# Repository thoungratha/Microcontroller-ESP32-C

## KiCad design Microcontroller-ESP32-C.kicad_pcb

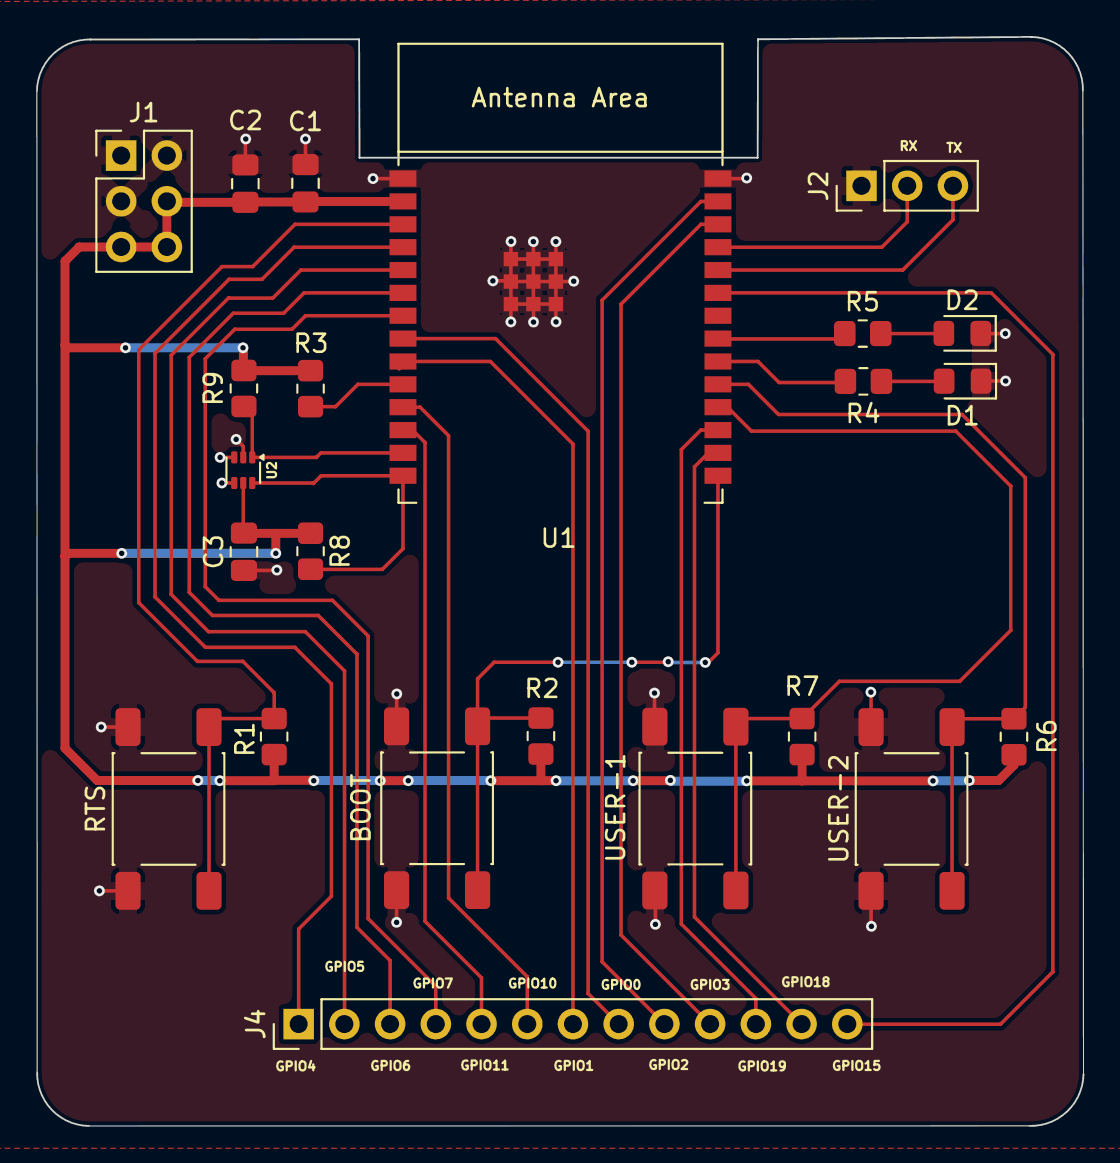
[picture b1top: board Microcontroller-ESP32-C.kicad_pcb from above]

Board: 2 copper layers, 58.1 x 60.5 mm, 23 parts (0 on the bottom side), 28 nets.

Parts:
BOOT: Button_Boot; SW_Push_1P1T_NO_E-Switch_TL3301NxxxxxG
C1: 10uF; C_0805_2012Metric_Pad1.18x1.45mm_HandSolder
C2, C3: 0.1uF; C_0805_2012Metric_Pad1.18x1.45mm_HandSolder
D1, D2: LED; LED_0805_2012Metric_Pad1.15x1.40mm_HandSolder
J1: Power_Connector; PinHeader_2x03_P2.54mm_Vertical
J2: Conn_01x03; PinHeader_1x03_P2.54mm_Vertical
J4: Conn_01x13; PinHeader_1x13_P2.54mm_Vertical
R1, R2, R3, R4, R5, R6, R7: 10k; R_0805_2012Metric_Pad1.20x1.40mm_HandSolder
R8, R9: 5k; R_0805_2012Metric_Pad1.20x1.40mm_HandSolder
RTS: Button_RST; SW_Push_1P1T_NO_E-Switch_TL3301NxxxxxG
U1: ESP32-C6-WROOM-1
U2: TMP112xxDRL; SOT-563
USER-1: USER_1; SW_Push_1P1T_NO_E-Switch_TL3301NxxxxxG
USER-2: USER_2; SW_Push_1P1T_NO_E-Switch_TL3301NxxxxxG

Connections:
3V3: C1.2, C2.2, C3.2, J1.4, J1.5, J1.6, R1.1, R2.2, R3.2, R6.2, R7.2, R8.1, R9.1, U1.2 (3V3), U2.5 (V+)
GND: BOOT.2, C1.1, C2.1, C3.1, D1.1 (K), D2.1 (K), J1.1, J1.2, J1.3, J2.1, RTS.1, U1.1 (GND), U1.28 (GND), U1.29 (GND), U2.2 (GND), U2.3 (ALERT), U2.4 (ADD0), USER-1.2, USER-2.2
GPIO0: J4.8, U1.8 (GPIO0/ADC1_CH0/XTAL_32K_P)
GPIO1: J4.7, U1.9 (GPIO1/ADC1_CH1/XTAL_32K_N)
GPIO2: J4.9, U1.27 (GPIO2/ADC1_CH2)
GPIO3: J4.10, U1.26 (GPIO3/ADC1_CH3)
GPIO4: J4.1, U1.4 (MTMS/GPIO4/ADC1_CH4)
GPIO5: J4.2, U1.5 (MTDI/GPIO5/ADC1_CH5)
GPIO6: J4.3, U1.6 (MTCK/GPIO6/ADC1_CH6)
GPIO7: J4.4, U1.7 (MTDO/GPIO7)
GPIO10: J4.6, U1.11 (GPIO10)
GPIO11: J4.5, U1.12 (GPIO11)
GPIO12: R9.2, U1.13 (GPIO12/USB_D-), U2.1 (SCL)
GPIO13: R8.2, U1.14 (GPIO13/USB_D+), U2.6 (SDA)
GPIO15: J4.13, U1.23 (GPIO15)
GPIO18: J4.12, U1.16 (GPIO18)
GPIO19: J4.11, U1.17 (GPIO19)
unnamed: D1.2 (A), R4.1
unnamed: D2.2 (A), R5.1
unnamed: R1.2, RTS.2, U1.3 (EN/CHIP_PU)
unnamed: R3.1, U1.10 (GPIO8)
unnamed: BOOT.1, R2.1, U1.15 (GPIO9)
unnamed: R7.1, U1.18 (GPIO20), USER-1.1
unnamed: R6.1, U1.19 (GPIO21), USER-2.1
unnamed: R4.2, U1.20 (GPIO22)
unnamed: R5.2, U1.21 (GPIO23)
UART0-RX: J2.3, U1.24 (U0RXD/GPIO17)
UART0-TX: J2.2, U1.25 (U0TXD/GPIO16)
